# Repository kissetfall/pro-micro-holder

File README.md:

## Pro micro holder 
Based on  PCB. Made specificaly for Dactyl Manuform.  
Two versions available: for Micro usb controller and for type-C.

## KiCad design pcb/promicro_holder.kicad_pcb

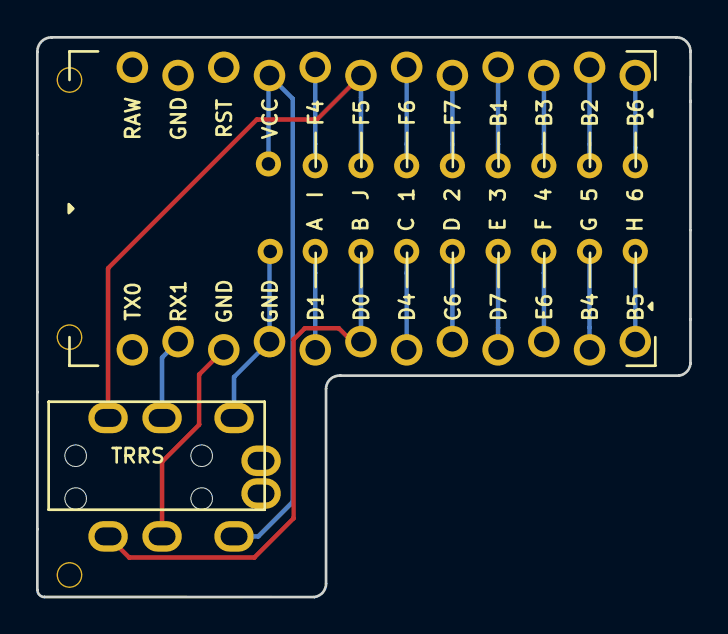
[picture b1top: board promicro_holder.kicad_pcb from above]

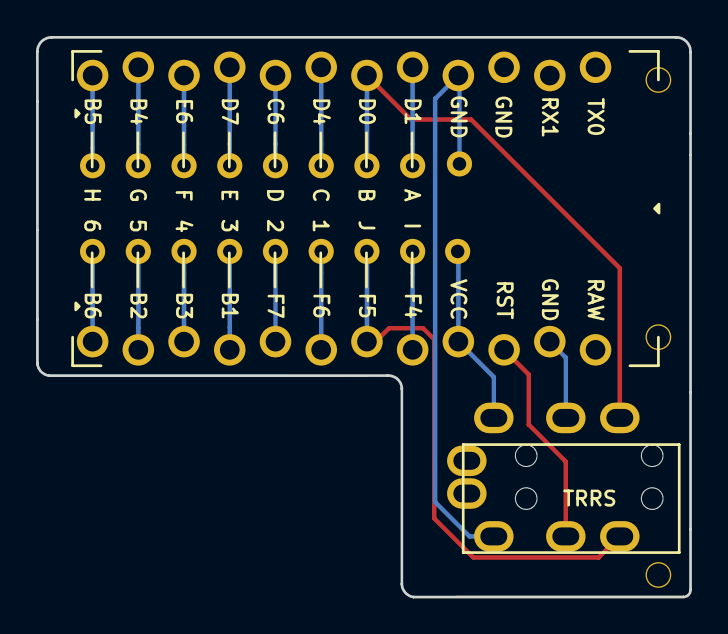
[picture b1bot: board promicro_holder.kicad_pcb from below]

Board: 2 copper layers, 36.3 x 31.1 mm, 7 parts (2 on the bottom side), 17 nets.

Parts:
H53, H53#2: MountingHole_Pad; 1pin_conn
J1, J6: MJ-4PP-9
J3, J4: Conn_01x08; PinHeader_1x08_P2.54mm_Vertical_rev2
U1: ProMicro; ArduinoProMicro-ZigZag_rev5

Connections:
GND: J1.C, J6.C, U1.3, U1.22, U1.23
X2: J4.2, U1.5
X3: J4.3, U1.7
X4: J4.4, U1.8
X5: J4.5, U1.9
X6: J4.6, U1.10
X7: J4.7, U1.11
X8: J4.8, U1.12
X9: J3.1, U1.20
Y1: J3.3, U1.18
Y2: J3.4, U1.17
Y3: J3.5, U1.16
Y4: J3.6, U1.15
Y5: J3.7, U1.14
Y6: J3.8, U1.13
dummyVCC: H53.1, H53#2.1, J1.D, J6.D, U1.4, U1.21
dummydata: J1.B, J6.B, U1.6, U1.19

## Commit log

2021-10-27 second commit
